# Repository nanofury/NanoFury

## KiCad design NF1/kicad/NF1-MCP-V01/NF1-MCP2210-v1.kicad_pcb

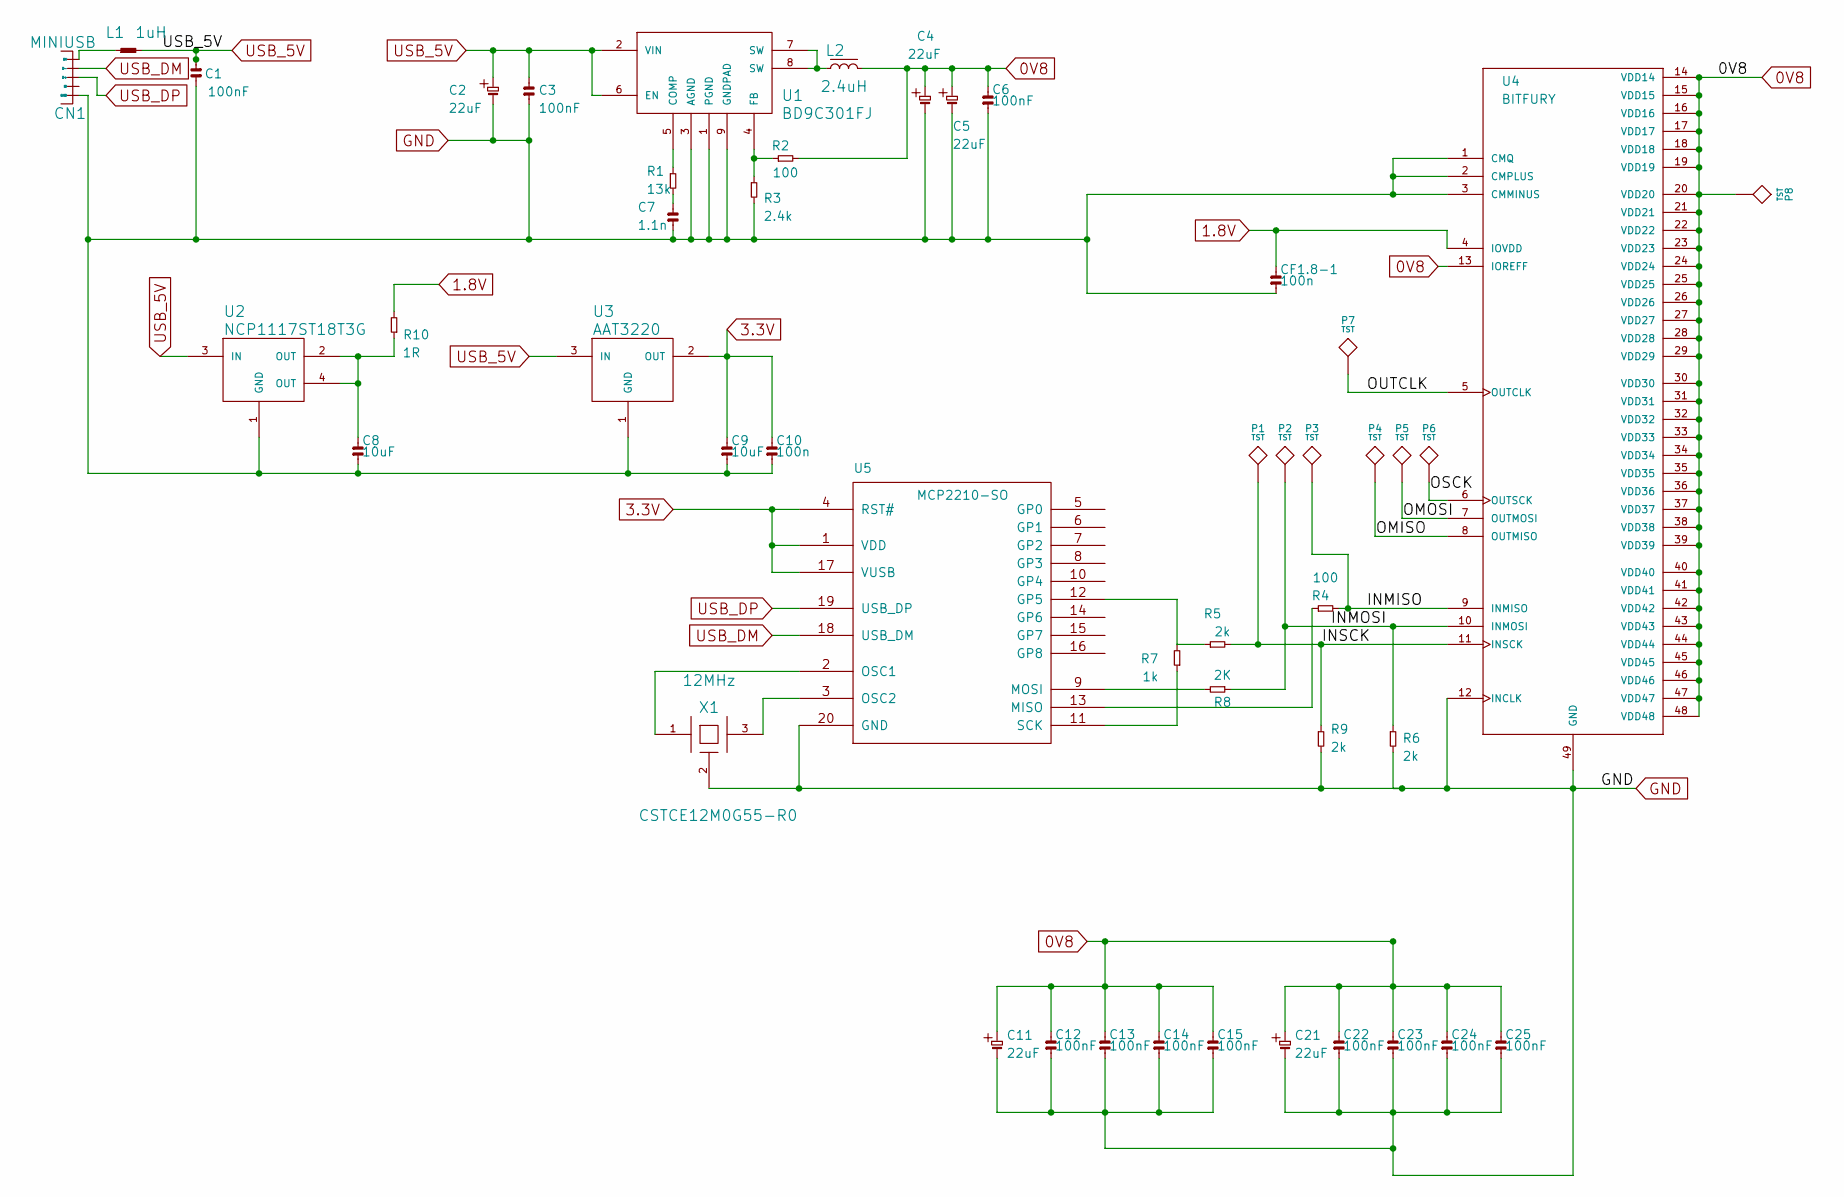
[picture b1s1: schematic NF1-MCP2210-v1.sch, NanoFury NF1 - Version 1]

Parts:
C1, C3, C6, C12, C13, C14, C15, C22, C23, C24, C25: 100nF; 0402
C2, C4, C5, C11, C21: 22uF; 0805
C7: 1.1n; 0402
C8, C9: 10uF; 0805
C10: 100n; 0402
CF1.8-1: 100n; 0402
CN1: MINIUSB; USBAPCB
L1: 1uH; 0402
L2: 2.4uH; 0630
P1, P2, P3, P4, P5, P6, P7, P8: TST; TP
R1: 13k; 0402
R2, R4: 100; 0402
R3: 2.4k; 0402
R5, R6, R9: 2k; 0402
R7: 1k; 0402
R8: 2K; 0402
R10: 1R; 0402
U1: BD9C301FJ; HTSOP-J8
U2: NCP1117ST18T3G; SOT-223
U3: AAT3220; SC59
U4: BITFURY; QFN48
U5: MCP2210-SO; SSOP-20
X1: 12MHz; CSTCE_G15C; Part Number CSTCE12M0G55-R0

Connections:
0V8: C4.1, C5.1, C6.1, C11.1, C12.1, C13.1, C14.1, C15.1, C21.1, C22.1, C23.1, C24.1, C25.1, L2.2, P8.1, R2.1, U4.13 (IOREFF), U4.14 (VDD14), U4.15 (VDD15), U4.16 (VDD16), U4.17 (VDD17), U4.18 (VDD18), U4.19 (VDD19), U4.20 (VDD20), U4.21 (VDD21), U4.22 (VDD22), U4.23 (VDD23), U4.24 (VDD24), U4.25 (VDD25), U4.26 (VDD26), U4.27 (VDD27), U4.28 (VDD28), U4.29 (VDD29), U4.30 (VDD30), U4.31 (VDD31), U4.32 (VDD32), U4.33 (VDD33), U4.34 (VDD34), U4.35 (VDD35), U4.36 (VDD36), U4.37 (VDD37), U4.38 (VDD38), U4.39 (VDD39), U4.40 (VDD40), U4.41 (VDD41), U4.42 (VDD42), U4.43 (VDD43), U4.44 (VDD44), U4.45 (VDD45), U4.46 (VDD46), U4.47 (VDD47), U4.48 (VDD48)
1.8V: CF1.8-1.1, R10.1, U4.4 (IOVDD)
3.3V: C9.1, C10.1, U3.2 (OUT), U5.1 (VDD), U5.4 (RST#), U5.17 (VUSB)
/INMISO: P3.1, R4.1, U4.9 (INMISO)
/INMOSI: P2.1, R6.2, R8.2, U4.10 (INMOSI)
/INSCK: P1.1, R5.1, R9.2, U4.11 (INSCK)
/OMISO: P4.1, U4.8 (OUTMISO)
/OMOSI: P5.1, U4.7 (OUTMOSI)
/OSCK: P6.1, U4.6 (OUTSCK)
/OUTCLK: P7.1, U4.5 (OUTCLK)
GND: C1.1, C2.2, C3.2, C4.2, C5.2, C6.2, C7.2, C8.2, C9.2, C10.2, C11.2, C12.2, C13.2, C14.2, C15.2, C21.2, C22.2, C23.2, C24.2, C25.2, CF1.8-1.2, CN1.5 (GND), R3.1, R6.1, R9.1, U1.1 (PGND), U1.3 (AGND), U1.9 (GNDPAD), U2.1 (GND), U3.1 (GND), U4.1 (CMQ), U4.2 (CMPLUS), U4.3 (CMMINUS), U4.12 (INCLK), U4.49 (GND), U5.20 (GND), X1.2 (GND)
unnamed: C7.1, R1.1
unnamed: R1.2, U1.5 (COMP)
unnamed: R7.2, U5.11 (SCK)
unnamed: R4.2, U5.13 (MISO)
unnamed: R8.1, U5.9 (MOSI)
unnamed: U5.2 (OSC1), X1.1
unnamed: R5.2, R7.1, U5.12 (GP5)
unnamed: U5.3 (OSC2), X1.3
unnamed: L2.1, U1.7 (SW), U1.8 (SW)
unnamed: R2.2, R3.2, U1.4 (FB)
unnamed: CN1.1 (5V), L1.1
unnamed: C8.1, R10.2, U2.2 (OUT), U2.4 (OUT)
USB_5V: C1.2, C2.1, C3.1, L1.2, U1.2 (VIN), U1.6 (EN), U2.3 (IN), U3.3 (IN)
USB_DM: CN1.2 (D-), U5.18 (USB_DM)
USB_DP: CN1.3 (D+), U5.19 (USB_DP)

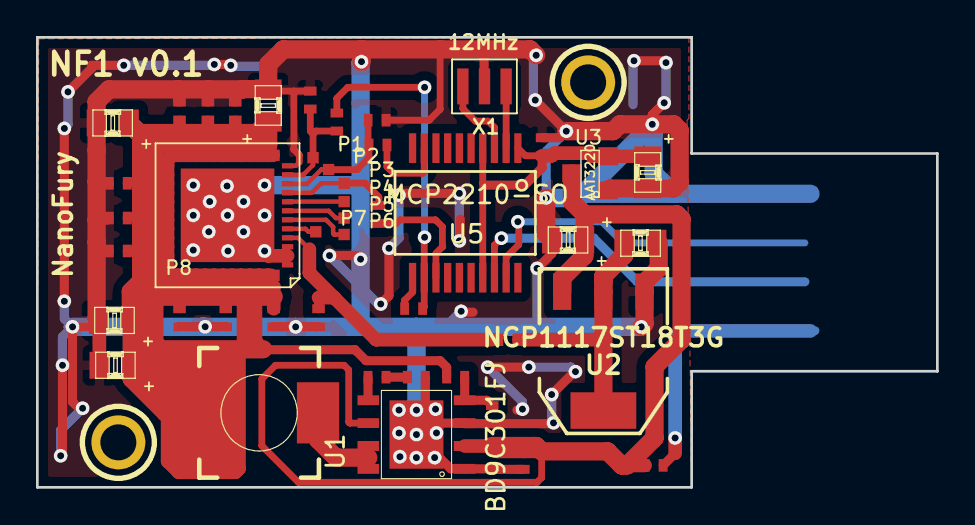
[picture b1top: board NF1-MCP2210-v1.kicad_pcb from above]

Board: 2 copper layers, 50.0 x 25.0 mm, 50 parts (1 on the bottom side), 26 nets.

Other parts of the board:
Hole2mm, Hole2mm1: P***; Hole2mm
